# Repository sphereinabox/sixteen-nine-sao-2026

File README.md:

# Sixteen-Nine SAO 2026
SAO with 16x9 LED matrix

Uses ISSI IS31FL3731 i2c to 16x9 charlieplex LED matrix driver, and WCH CH32V003 microcontroller.

By defaul the SAO i2c connections go to ch32v003, but can be changed with solder jumpers to connect the LED matrix driver i2c to SAO i2c directly.

## SAO Operation
TODO:
I'd like to switch the active animation, and maybe configure it using the two buttons
also be able to command animations from badge i2c

## Included Animations
 * Bounce: Kind of like bouncing DVD logo animation
 * Plasma
 * Scrolling text
 * Conways Game of Life

## Hardware

[Schematic PDF](kicad/v1/schematic.pdf)

This SAO has:
 1. 16x9 LED matrix
 2. IS31FL3731 I2C LED Driver
 3. CH32V003 QFN20
 4. 2 Push-buttons
 5. One more LED

 The SAO I2C connection goes to the ch32v003 microcontroller, which then has other pins to talk to the IS31 LED driver.

### Back Side

### Jumpers JP4, JP5
Connect the SAO I2C to the IS31 LED driver directly by briding the JP4/JP5

### Jumpers JP6, JP7
JP6 selects which pins are connected to the IS31_INT pin
 - 1-2 bridged (default) SAO GPIO1 connects to IS31_INT
 - 2-3 bridged, connect ch32v003 pin `PA1` to IS31_INT

JP7 selects wich pins are connected to IS31_IN analog input pin for audio-reactive animations
 - 1-2 bridged (default) SAO GPIO2 connects to IS31_IN
 - 2-3 bridged, connect ch32v003 pin `PA2` to IS31_IN

## Ch32V003 software

Uses ch32fun: https://github.com/cnlohr/ch32fun

See [Software Readme](software/ch32/README.md) for more

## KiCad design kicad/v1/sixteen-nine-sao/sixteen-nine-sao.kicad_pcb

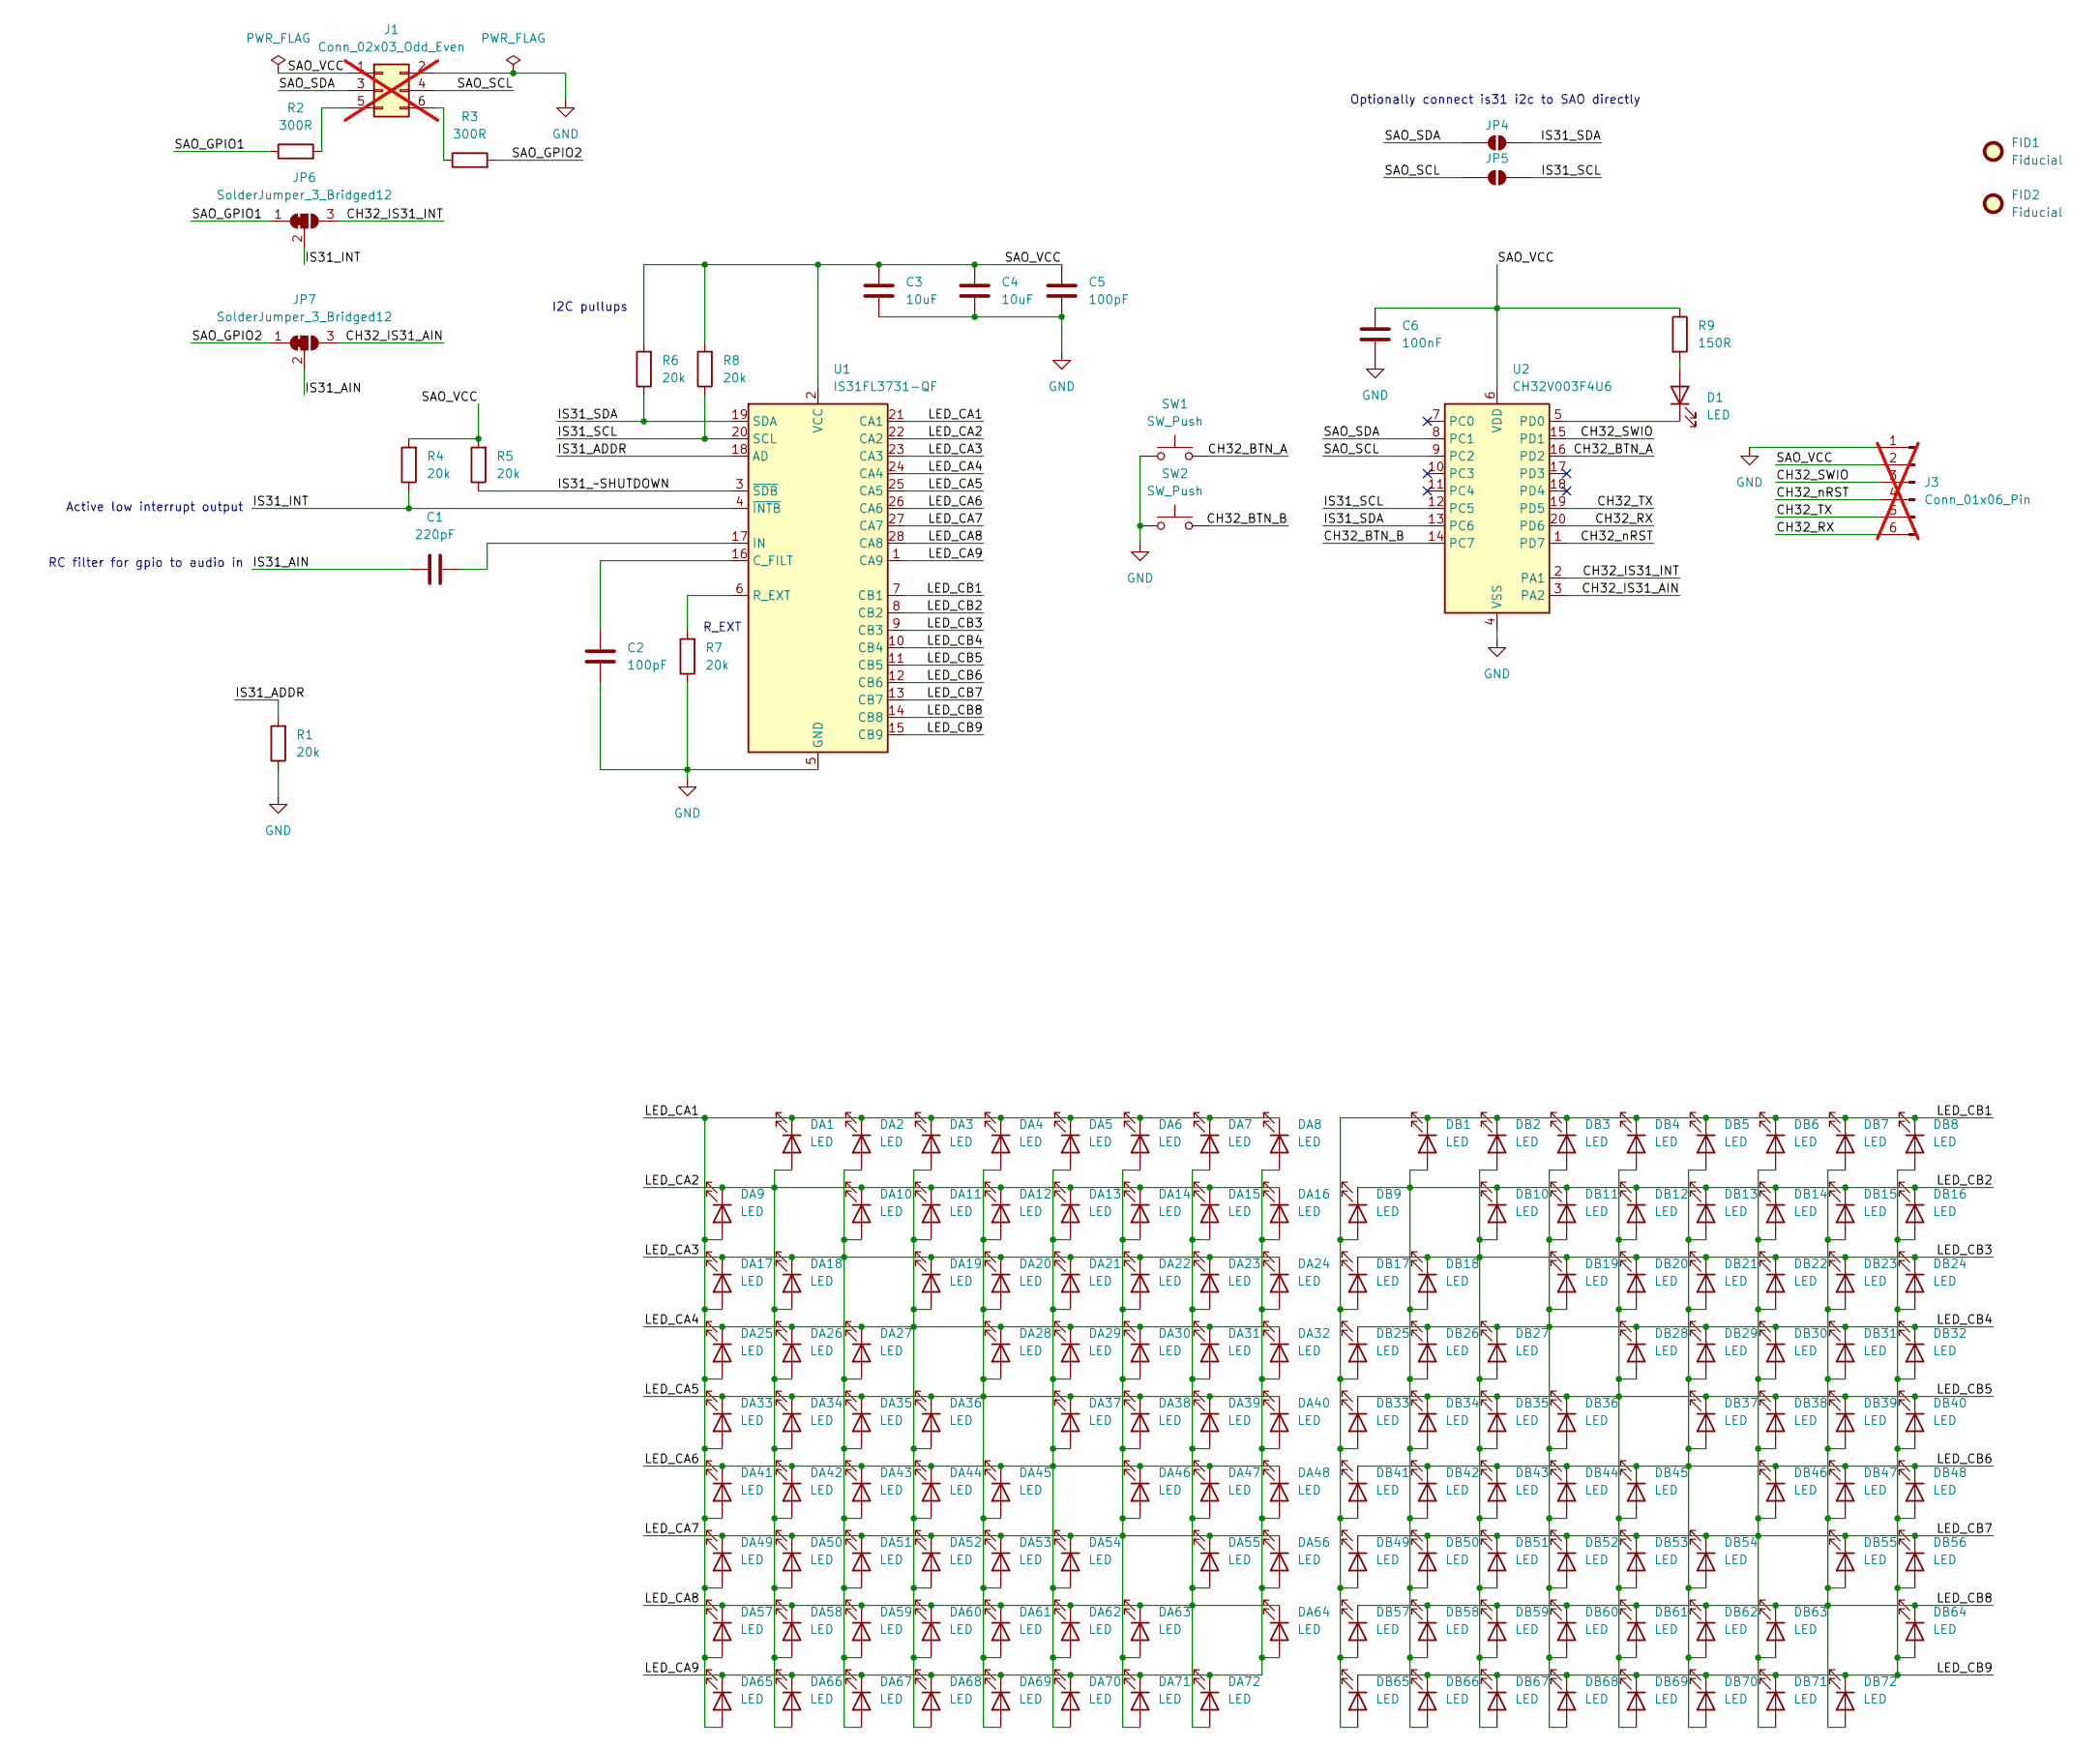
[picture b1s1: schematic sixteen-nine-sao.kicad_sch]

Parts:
C1: 220pF; C_0402_1005Metric; LCSC C1530
C2, C5: 100pF; C_0402_1005Metric; LCSC C1546
C3, C4: 10uF; C_0603_1608Metric; LCSC C19702
C6: 100nF; C_0402_1005Metric; LCSC C1525
D1: LED; LED_0603_1608Metric; LCSC C2290
DA1, DA2, DA3, DA4, DA5, DA6, DA7, DA8, DA9, DA10, DA11, DA12, DA13, DA14, DA15, DA16, DA17, DA18, DA19, DA20, DA21, DA22, DA23, DA24, DA25, DA26, DA27, DA28, DA29, DA30, DA31, DA32, DA33, DA34, DA35, DA36, DA37, DA38, DA39, DA40, DA41, DA42, DA43, DA44, DA45, DA46, DA47, DA48, DA49, DA50, DA51, DA52, DA53, DA54, DA55, DA56, DA57, DA58, DA59, DA60, DA61, DA62, DA63, DA64, DA65, DA66, DA67, DA68, DA69, DA70, DA71, DA72: LED; LED_0603_1608Metric; LCSC C2290
DB1, DB2, DB3, DB4, DB5, DB6, DB7, DB8, DB9, DB10, DB11, DB12, DB13, DB14, DB15, DB16, DB17, DB18, DB19, DB20, DB21, DB22, DB23, DB24, DB25, DB26, DB27, DB28, DB29, DB30, DB31, DB32, DB33, DB34, DB35, DB36, DB37, DB38, DB39, DB40, DB41, DB42, DB43, DB44, DB45, DB46, DB47, DB48, DB49, DB50, DB51, DB52, DB53, DB54, DB55, DB56, DB57, DB58, DB59, DB60, DB61, DB62, DB63, DB64, DB65, DB66, DB67, DB68, DB69, DB70, DB71, DB72: LED; LED_0603_1608Metric; LCSC C2290
FID1, FID2: Fiducial; Fiducial_0.75mm_Mask1.5mm
J1: Conn_02x03_Odd_Even; IDC-Header_2x03_P2.54mm_Vertical; not fitted
J3: Conn_01x06_Pin; PinHeader_1x06_P2.00mm_Vertical; not fitted
JP4, JP5: SolderJumper_2_Open; SolderJumper-2_P1.3mm_Open_TrianglePad1.0x1.5mm
JP6, JP7: SolderJumper_3_Bridged12; SolderJumper-3_P1.3mm_Bridged12_RoundedPad1.0x1.5mm_NumberL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
R1, R4, R5, R6, R7, R8: 20k; R_0603_1608Metric; LCSC C4184
R2, R3: 300R; R_0603_1608Metric; LCSC C23025
R9: 150R; R_0603_1608Metric; LCSC C22808
SW1, SW2: SW_Push; SW_SPST_TS-1088-xR020; LCSC C720477
U1: IS31FL3731-QF; QFN-28-1EP_4x4mm_P0.4mm_EP2.3x2.3mm; LCSC C191206
U2: CH32V003F4U6; QFN-20-1EP_3x3mm_P0.4mm_EP1.65x1.65mm; LCSC C5299908

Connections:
/CH32_BTN_A: SW1.2, U2.16 (PD2)
/CH32_BTN_B: SW2.2, U2.14 (PC7)
/CH32_IS31_AIN: JP7.3 (B), U2.3 (PA2)
/CH32_IS31_INT: JP6.3 (B), U2.2 (PA1)
/CH32_RX: J3.6, U2.20 (PD6)
/CH32_SWIO: J3.3, U2.15 (PD1)
/CH32_TX: J3.5, U2.19 (PD5)
/CH32_nRST: J3.4, U2.1 (PD7)
/IS31_ADDR: R1.2, U1.18 (AD)
/IS31_AIN: C1.1, JP7.2 (C)
/IS31_INT: JP6.2 (C), R4.1, U1.4 (~INTB)
/IS31_SCL: JP5.2 (B), R8.1, U1.20 (SCL), U2.12 (PC5)
/IS31_SDA: JP4.2 (B), R6.1, U1.19 (SDA), U2.13 (PC6)
/IS31_~SHUTDOWN: R5.1, U1.3 (~SDB)
/LED_CA1: DA1.1 (K), DA2.1 (K), DA3.1 (K), DA4.1 (K), DA5.1 (K), DA6.1 (K), DA7.1 (K), DA8.1 (K), DA9.2 (A), DA17.2 (A), DA25.2 (A), DA33.2 (A), DA41.2 (A), DA49.2 (A), DA57.2 (A), DA65.2 (A), U1.21 (CA1)
/LED_CA2: DA1.2 (A), DA9.1 (K), DA10.1 (K), DA11.1 (K), DA12.1 (K), DA13.1 (K), DA14.1 (K), DA15.1 (K), DA16.1 (K), DA18.2 (A), DA26.2 (A), DA34.2 (A), DA42.2 (A), DA50.2 (A), DA58.2 (A), DA66.2 (A), U1.22 (CA2)
/LED_CA3: DA2.2 (A), DA10.2 (A), DA17.1 (K), DA18.1 (K), DA19.1 (K), DA20.1 (K), DA21.1 (K), DA22.1 (K), DA23.1 (K), DA24.1 (K), DA27.2 (A), DA35.2 (A), DA43.2 (A), DA51.2 (A), DA59.2 (A), DA67.2 (A), U1.23 (CA3)
/LED_CA4: DA3.2 (A), DA11.2 (A), DA19.2 (A), DA25.1 (K), DA26.1 (K), DA27.1 (K), DA28.1 (K), DA29.1 (K), DA30.1 (K), DA31.1 (K), DA32.1 (K), DA36.2 (A), DA44.2 (A), DA52.2 (A), DA60.2 (A), DA68.2 (A), U1.24 (CA4)
/LED_CA5: DA4.2 (A), DA12.2 (A), DA20.2 (A), DA28.2 (A), DA33.1 (K), DA34.1 (K), DA35.1 (K), DA36.1 (K), DA37.1 (K), DA38.1 (K), DA39.1 (K), DA40.1 (K), DA45.2 (A), DA53.2 (A), DA61.2 (A), DA69.2 (A), U1.25 (CA5)
/LED_CA6: DA5.2 (A), DA13.2 (A), DA21.2 (A), DA29.2 (A), DA37.2 (A), DA41.1 (K), DA42.1 (K), DA43.1 (K), DA44.1 (K), DA45.1 (K), DA46.1 (K), DA47.1 (K), DA48.1 (K), DA54.2 (A), DA62.2 (A), DA70.2 (A), U1.26 (CA6)
/LED_CA7: DA6.2 (A), DA14.2 (A), DA22.2 (A), DA30.2 (A), DA38.2 (A), DA46.2 (A), DA49.1 (K), DA50.1 (K), DA51.1 (K), DA52.1 (K), DA53.1 (K), DA54.1 (K), DA55.1 (K), DA56.1 (K), DA63.2 (A), DA71.2 (A), U1.27 (CA7)
/LED_CA8: DA7.2 (A), DA15.2 (A), DA23.2 (A), DA31.2 (A), DA39.2 (A), DA47.2 (A), DA55.2 (A), DA57.1 (K), DA58.1 (K), DA59.1 (K), DA60.1 (K), DA61.1 (K), DA62.1 (K), DA63.1 (K), DA64.1 (K), DA72.2 (A), U1.28 (CA8)
/LED_CA9: DA8.2 (A), DA16.2 (A), DA24.2 (A), DA32.2 (A), DA40.2 (A), DA48.2 (A), DA56.2 (A), DA64.2 (A), DA65.1 (K), DA66.1 (K), DA67.1 (K), DA68.1 (K), DA69.1 (K), DA70.1 (K), DA71.1 (K), DA72.1 (K), U1.1 (CA9)
/LED_CB1: DB1.1 (K), DB2.1 (K), DB3.1 (K), DB4.1 (K), DB5.1 (K), DB6.1 (K), DB7.1 (K), DB8.1 (K), DB9.2 (A), DB17.2 (A), DB25.2 (A), DB33.2 (A), DB41.2 (A), DB49.2 (A), DB57.2 (A), DB65.2 (A), U1.7 (CB1)
/LED_CB2: DB1.2 (A), DB9.1 (K), DB10.1 (K), DB11.1 (K), DB12.1 (K), DB13.1 (K), DB14.1 (K), DB15.1 (K), DB16.1 (K), DB18.2 (A), DB26.2 (A), DB34.2 (A), DB42.2 (A), DB50.2 (A), DB58.2 (A), DB66.2 (A), U1.8 (CB2)
/LED_CB3: DB2.2 (A), DB10.2 (A), DB17.1 (K), DB18.1 (K), DB19.1 (K), DB20.1 (K), DB21.1 (K), DB22.1 (K), DB23.1 (K), DB24.1 (K), DB27.2 (A), DB35.2 (A), DB43.2 (A), DB51.2 (A), DB59.2 (A), DB67.2 (A), U1.9 (CB3)
/LED_CB4: DB3.2 (A), DB11.2 (A), DB19.2 (A), DB25.1 (K), DB26.1 (K), DB27.1 (K), DB28.1 (K), DB29.1 (K), DB30.1 (K), DB31.1 (K), DB32.1 (K), DB36.2 (A), DB44.2 (A), DB52.2 (A), DB60.2 (A), DB68.2 (A), U1.10 (CB4)
/LED_CB5: DB4.2 (A), DB12.2 (A), DB20.2 (A), DB28.2 (A), DB33.1 (K), DB34.1 (K), DB35.1 (K), DB36.1 (K), DB37.1 (K), DB38.1 (K), DB39.1 (K), DB40.1 (K), DB45.2 (A), DB53.2 (A), DB61.2 (A), DB69.2 (A), U1.11 (CB5)
/LED_CB6: DB5.2 (A), DB13.2 (A), DB21.2 (A), DB29.2 (A), DB37.2 (A), DB41.1 (K), DB42.1 (K), DB43.1 (K), DB44.1 (K), DB45.1 (K), DB46.1 (K), DB47.1 (K), DB48.1 (K), DB54.2 (A), DB62.2 (A), DB70.2 (A), U1.12 (CB6)
/LED_CB7: DB6.2 (A), DB14.2 (A), DB22.2 (A), DB30.2 (A), DB38.2 (A), DB46.2 (A), DB49.1 (K), DB50.1 (K), DB51.1 (K), DB52.1 (K), DB53.1 (K), DB54.1 (K), DB55.1 (K), DB56.1 (K), DB63.2 (A), DB71.2 (A), U1.13 (CB7)
/LED_CB8: DB7.2 (A), DB15.2 (A), DB23.2 (A), DB31.2 (A), DB39.2 (A), DB47.2 (A), DB55.2 (A), DB57.1 (K), DB58.1 (K), DB59.1 (K), DB60.1 (K), DB61.1 (K), DB62.1 (K), DB63.1 (K), DB64.1 (K), DB72.2 (A), U1.14 (CB8)
/LED_CB9: DB8.2 (A), DB16.2 (A), DB24.2 (A), DB32.2 (A), DB40.2 (A), DB48.2 (A), DB56.2 (A), DB64.2 (A), DB65.1 (K), DB66.1 (K), DB67.1 (K), DB68.1 (K), DB69.1 (K), DB70.1 (K), DB71.1 (K), DB72.1 (K), U1.15 (CB9)
/SAO_GPIO1: JP6.1 (A), R2.1
/SAO_GPIO2: JP7.1 (A), R3.2
/SAO_SCL: J1.4, JP5.1 (A), U2.9 (PC2)
/SAO_SDA: J1.3, JP4.1 (A), U2.8 (PC1)
/SAO_VCC: C3.1, C4.1, C5.1, C6.1, J1.1, J3.2, R4.2, R5.2, R6.2, R8.2, R9.1, U1.2 (VCC), U2.6 (VDD)
GND: C2.2, C3.2, C4.2, C5.2, C6.2, J1.2, J3.1, R1.1, R7.1, SW1.1, SW2.1, U1.5 (GND), U1.29 (GND), U2.4 (VSS), U2.21 (VSS)
unnamed: D1.2 (A), R9.2
unnamed: D1.1 (K), U2.5 (PD0)
unnamed: J1.5, R2.2
unnamed: J1.6, R3.1
unnamed: C2.1, U1.16 (C_FILT)
unnamed: C1.2, U1.17 (IN)
unnamed: R7.2, U1.6 (R_EXT)

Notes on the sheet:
R_EXT
I2C pullups
RC filter for gpio to audio in
Optionally connect is31 i2c to SAO directly
Active low interrupt output

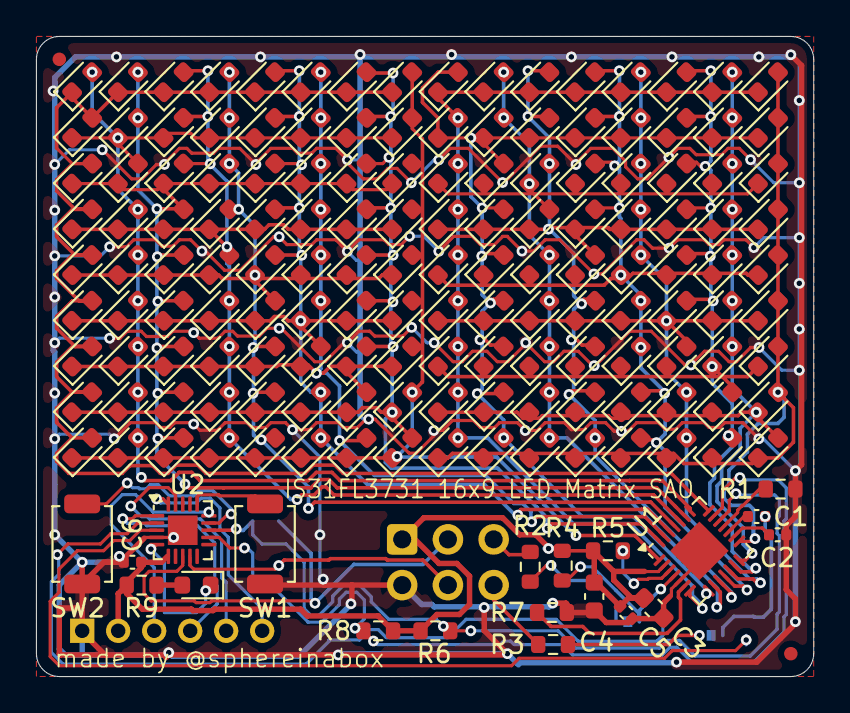
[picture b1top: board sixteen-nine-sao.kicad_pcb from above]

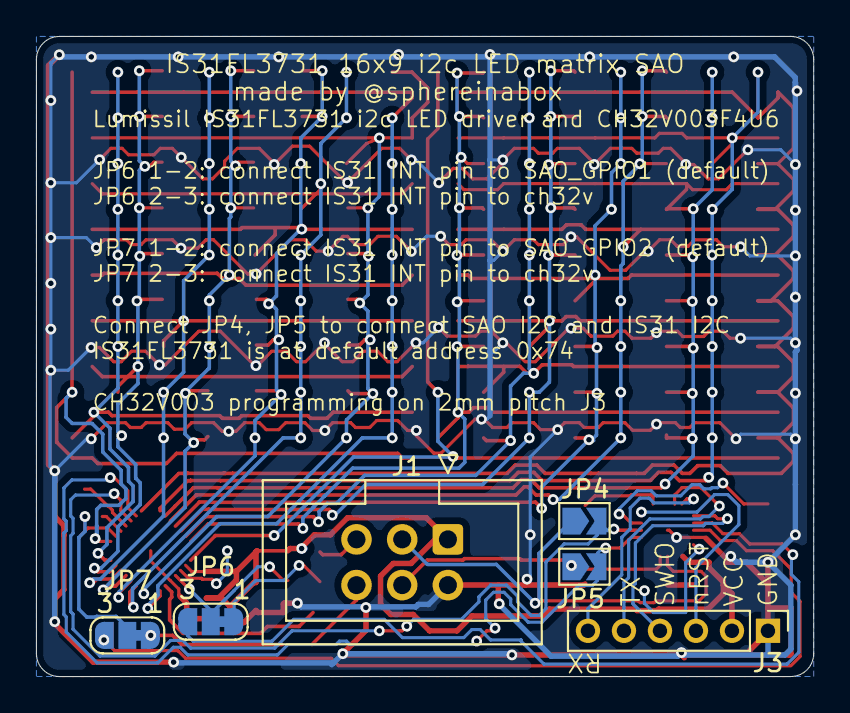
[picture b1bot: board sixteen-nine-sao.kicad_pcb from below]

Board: 2 copper layers, 43.2 x 35.6 mm, 172 parts (6 on the bottom side), 45 nets.

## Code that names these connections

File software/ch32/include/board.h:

#ifndef _BOARD_H
#define _BOARD_H

#include "ch32fun.h"

// https://badge.team/docs/standards/sao/ describes i2c eeprom at address 0x50
// 0x50 is decimal 80
#define SAO_I2C_ADDRESS 0x50
// the header is bytes at address 0 through 35
#define SAO_REG_BUTTON_BITS 48
#define SAO_REG_LED 49
#define SAO_REG_ANIMATION_CHOICE 50
#define SAO_ANIMATION_CHOICE_STATIC 0
#define SAO_ANIMATION_CHOICE_CONWAYS 1
#define SAO_ANIMATION_CHOICE_TEXT_SCROLL 2
#define SAO_ANIMATION_CHOICE_PLASMA 3
#define SAO_ANIMATION_CHOICE_BOUNCE 4
#define SAO_REG_ANIM_INTENSITY_MAX 51
// #define SAO_REG_ANIM_CONWAY_SLOWDOWN 52
// #define SAO_REG_ANIM_CONWAY_OPTIONS 53
// #define SAO_REG_ANIM_TEXT_SLOWDOWN 55
#define SAO_REG_DISPLAY_OR_TEXT 64


#define IS31_PIN_SCL PC5
#define IS31_PIN_SDA PC6
// by default not connected to is31. Switch solder jump JP6 to pins 2-3 to connect
#define IS31_PIN_INT PA1
// by default not connected to is31. Switch solder jump JP7 to pins 2-3 to connect
#define IS31_PIN_AIN PA2

#define SAO_PIN_SCL PC2
#define SAO_PIN_SDA PC1

// LED lights when pin low
#define PIN_LED PD0

// right button
#define PIN_BTN_A PD2
// left button
#define PIN_BTN_B PC7

// these are on header on bottom left corner:
#define PIN_TX PD5
#define PIN_RX PD6

// as shown in datasheet, 16x9 display, split into 8 column 9 row halves left/right
#define IS31_DISPLAY_LAYOUT 1
// adafruit charlieplex bonnet is 16x8 and has flipped rows/columns from what I expect
// #define IS31_DISPLAY_LAYOUT 2

#if IS31_DISPLAY_LAYOUT == 1
#define IS31_WIDTH 16
#define IS31_HEIGHT 9

#elif IS31_DISPLAY_LAYOUT == 2
#define IS31_WIDTH 16
#define IS31_HEIGHT 8

#endif


#endif
